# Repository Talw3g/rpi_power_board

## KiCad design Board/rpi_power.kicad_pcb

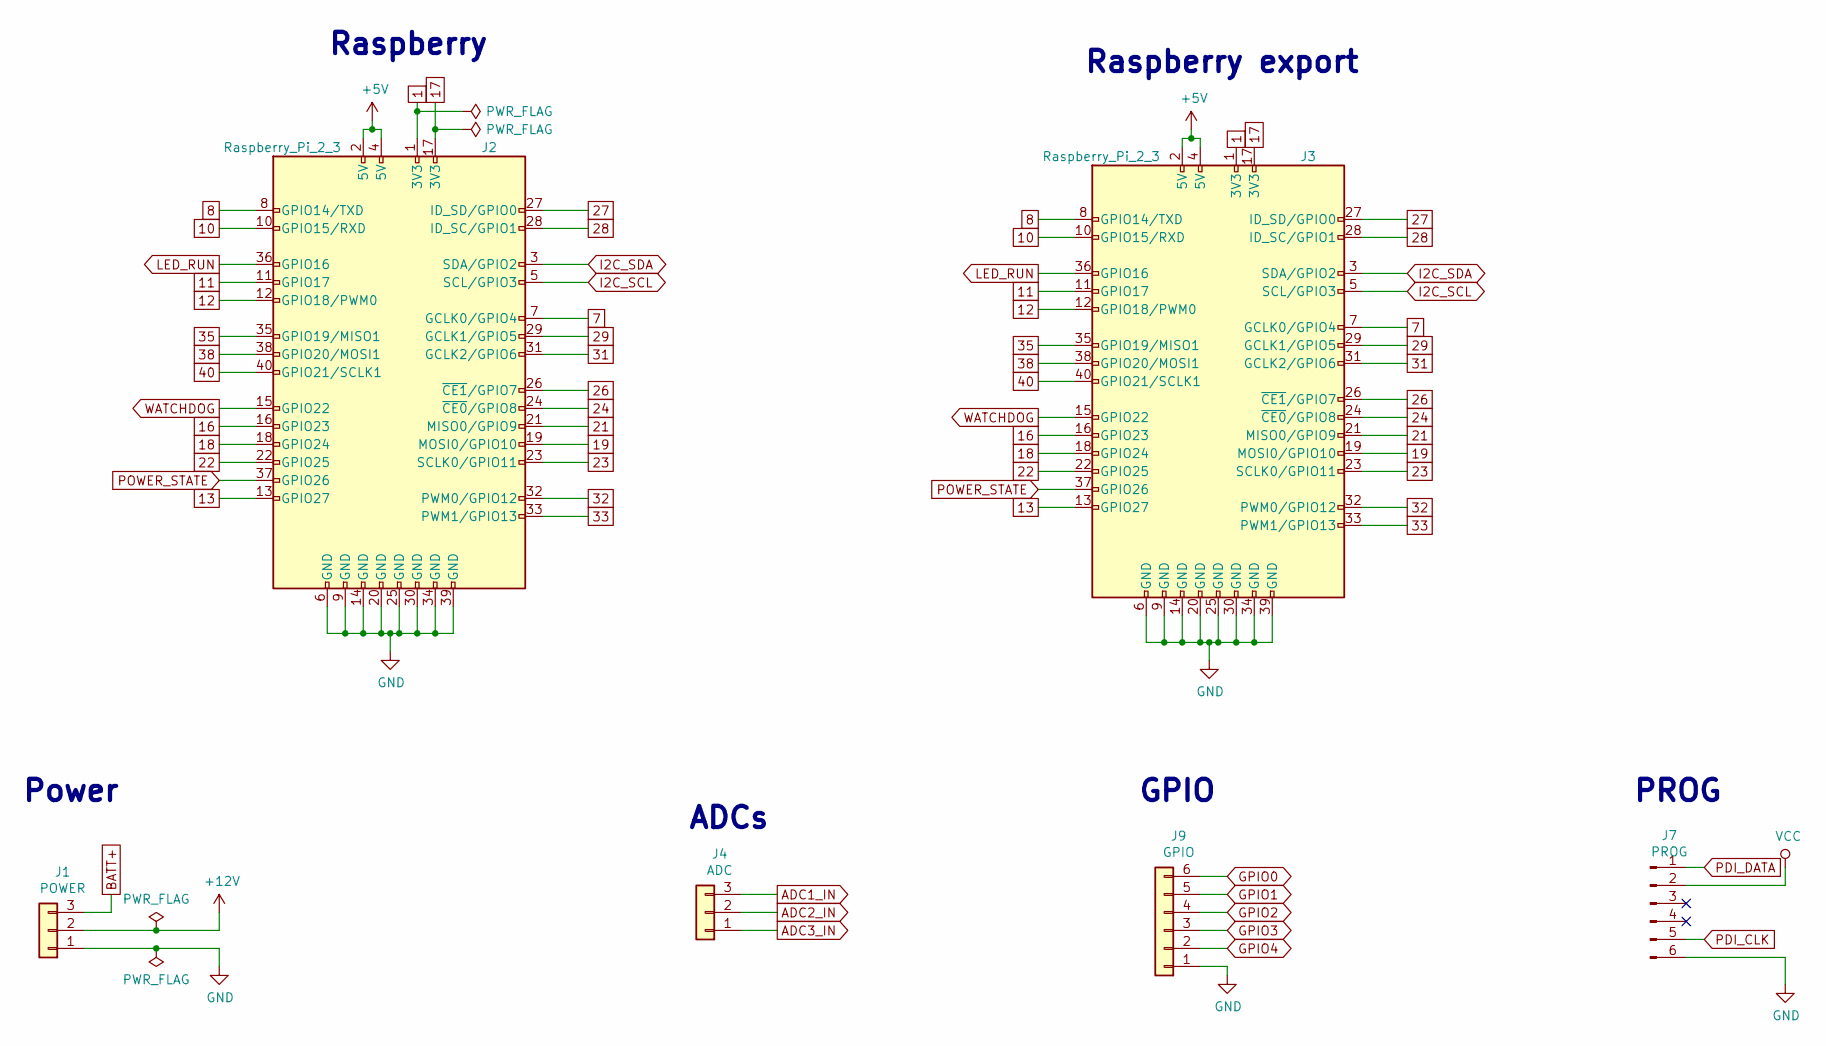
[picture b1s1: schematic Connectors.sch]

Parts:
J1: POWER; mpt_0,5-3-2,54; Farnell 3041360
J2: Raspberry_Pi_2_3; PinSocket_2x20_P2.54mm_Vertical_SMD; Farnell 2847933
J3: Raspberry_Pi_2_3; PinHeader_2x20_P2.54mm_Vertical_SMD; Farnell 2751390
J4: ADC; mpt_0,5-3-2,54; Farnell 3041360
J7: PROG; PinHeader_2x03_P2.54mm_Vertical
J9: GPIO; mpt_0,5-6-2,54; Farnell 3041426

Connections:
1: J2.1 (3V3), J3.1 (3V3)
7: J2.7 (GCLK0/GPIO4), J3.7 (GCLK0/GPIO4)
8: J2.8 (GPIO14/TXD), J3.8 (GPIO14/TXD)
10: J2.10 (GPIO15/RXD), J3.10 (GPIO15/RXD)
11: J2.11 (GPIO17), J3.11 (GPIO17)
12: J2.12 (GPIO18/PWM0), J3.12 (GPIO18/PWM0)
13: J2.13 (GPIO27), J3.13 (GPIO27)
16: J2.16 (GPIO23), J3.16 (GPIO23)
17: J2.17 (3V3), J3.17 (3V3)
18: J2.18 (GPIO24), J3.18 (GPIO24)
19: J2.19 (MOSI0/GPIO10), J3.19 (MOSI0/GPIO10)
21: J2.21 (MISO0/GPIO9), J3.21 (MISO0/GPIO9)
22: J2.22 (GPIO25), J3.22 (GPIO25)
23: J2.23 (SCLK0/GPIO11), J3.23 (SCLK0/GPIO11)
24: J2.24 (~CE0~/GPIO8), J3.24 (~CE0~/GPIO8)
26: J2.26 (~CE1~/GPIO7), J3.26 (~CE1~/GPIO7)
27: J2.27 (ID_SD/GPIO0), J3.27 (ID_SD/GPIO0)
28: J2.28 (ID_SC/GPIO1), J3.28 (ID_SC/GPIO1)
29: J2.29 (GCLK1/GPIO5), J3.29 (GCLK1/GPIO5)
31: J2.31 (GCLK2/GPIO6), J3.31 (GCLK2/GPIO6)
32: J2.32 (PWM0/GPIO12), J3.32 (PWM0/GPIO12)
33: J2.33 (PWM1/GPIO13), J3.33 (PWM1/GPIO13)
35: J2.35 (GPIO19/MISO1), J3.35 (GPIO19/MISO1)
38: J2.38 (GPIO20/MOSI1), J3.38 (GPIO20/MOSI1)
40: J2.40 (GPIO21/SCLK1), J3.40 (GPIO21/SCLK1)
+5V: J2.2 (5V), J2.4 (5V), J3.2 (5V), J3.4 (5V); also elsewhere on the board
+12V: J1.2; also elsewhere on the board
ADC1_IN: J4.3; also elsewhere on the board
ADC2_IN: J4.2; also elsewhere on the board
ADC3_IN: J4.1; also elsewhere on the board
BATT+: J1.3; also elsewhere on the board
GND: J1.1, J2.6 (GND), J2.9 (GND), J2.14 (GND), J2.20 (GND), J2.25 (GND), J2.30 (GND), J2.34 (GND), J2.39 (GND), J3.6 (GND), J3.9 (GND), J3.14 (GND), J3.20 (GND), J3.25 (GND), J3.30 (GND), J3.34 (GND), J3.39 (GND), J7.6, J9.1; also elsewhere on the board
GPIO0: J9.6; also elsewhere on the board
GPIO1: J9.5; also elsewhere on the board
GPIO2: J9.4; also elsewhere on the board
GPIO3: J9.3; also elsewhere on the board
GPIO4: J9.2; also elsewhere on the board
I2C_SCL: J2.5 (SCL/GPIO3), J3.5 (SCL/GPIO3); also elsewhere on the board
I2C_SDA: J2.3 (SDA/GPIO2), J3.3 (SDA/GPIO2); also elsewhere on the board
LED_RUN: J2.36 (GPIO16), J3.36 (GPIO16); also elsewhere on the board
PDI_CLK: J7.5; also elsewhere on the board
PDI_DATA: J7.1; also elsewhere on the board
POWER_STATE: J2.37 (GPIO26), J3.37 (GPIO26); also elsewhere on the board
VCC: J7.2; also elsewhere on the board
WATCHDOG: J2.15 (GPIO22), J3.15 (GPIO22); also elsewhere on the board

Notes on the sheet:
Raspberry
Power
ADCs
PROG
GPIO
Raspberry export

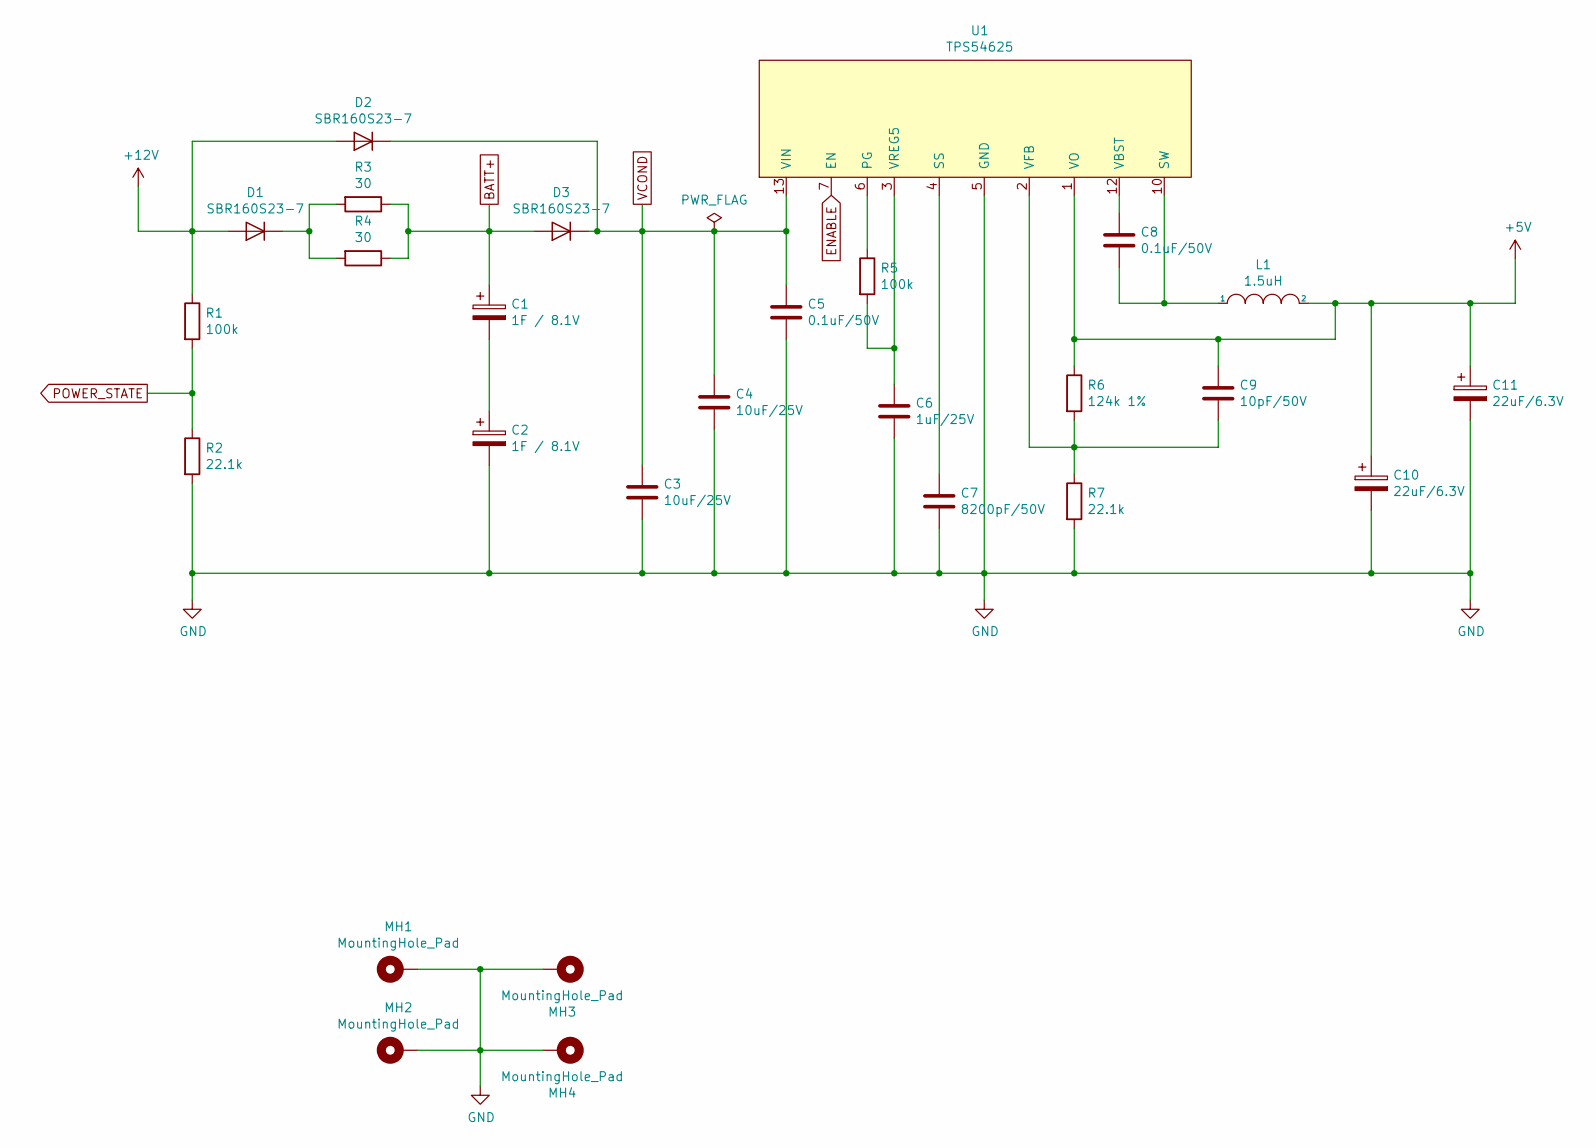
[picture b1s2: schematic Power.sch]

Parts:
C1, C2: 1F / 8.1V; SCMR22J105SRBA0_vertical; Farnell 2856949
C3, C4: 10uF/25V; C_0805_2012Metric_Pad1.15x1.40mm_HandSolder
C5, C8: 0.1uF/50V; C_0603_1608Metric_Pad1.05x0.95mm_HandSolder
C6: 1uF/25V; C_0805_2012Metric_Pad1.15x1.40mm_HandSolder
C7: 8200pF/50V; C_0603_1608Metric_Pad1.05x0.95mm_HandSolder
C9: 10pF/50V; C_0603_1608Metric_Pad1.05x0.95mm_HandSolder
C10, C11: 22uF/6.3V; Tantalum_SMD_3216_KEMET_T491_HandSolder; Farnell 2321204
D1, D2, D3: SBR160S23-7; D_SOT-23_ANK; Farnell 1863724
L1: 1.5uH; L_7.1x6.5_H3; Farnell 2215610
MH1, MH2, MH3, MH4: MountingHole_Pad; MountingHole_M3-5.8_Pad_Via
R1, R5: 100k; R_0603_1608Metric_Pad1.05x0.95mm_HandSolder
R2, R7: 22.1k; R_0603_1608Metric_Pad1.05x0.95mm_HandSolder
R3, R4: 30; TE_SM5; Farnell 2331667
R6: 124k 1%; R_0603_1608Metric_Pad1.05x0.95mm_HandSolder
U1: TPS54625; HTSSOP-14-PWP_Handsolder; Farnell 2361244

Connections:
+5V: C9.1, C10.1, C11.1, L1.2, R6.1, U1.1 (VO); also elsewhere on the board
+12V: D1.2 (A), D2.2 (A), R1.1; also elsewhere on the board
BATT+: C1.1, D3.2 (A), R3.1, R4.1; also elsewhere on the board
ENABLE: U1.7 (EN); also elsewhere on the board
GND: C2.2, C3.2, C4.2, C5.2, C6.2, C7.2, C10.2, C11.2, MH1.1, MH2.1, MH3.1, MH4.1, R2.2, R7.2, U1.5 (GND), U1.8 (GND), U1.9 (GND), U1.15 (GND); also elsewhere on the board
unnamed: C1.2, C2.1
unnamed: C6.1, R5.2, U1.3 (VREG5)
unnamed: C7.1, U1.4 (SS)
unnamed: C8.1, U1.12 (VBST)
unnamed: C8.2, L1.1, U1.10 (SW), U1.11 (SW)
unnamed: C9.2, R6.2, R7.1, U1.2 (VFB)
unnamed: D1.1 (K), R3.2, R4.2
unnamed: R5.1, U1.6 (PG)
POWER_STATE: R1.2, R2.1; also elsewhere on the board
VCOND: C3.1, C4.1, C5.1, D2.1 (K), D3.1 (K), U1.13 (VIN), U1.14 (VIN); also elsewhere on the board

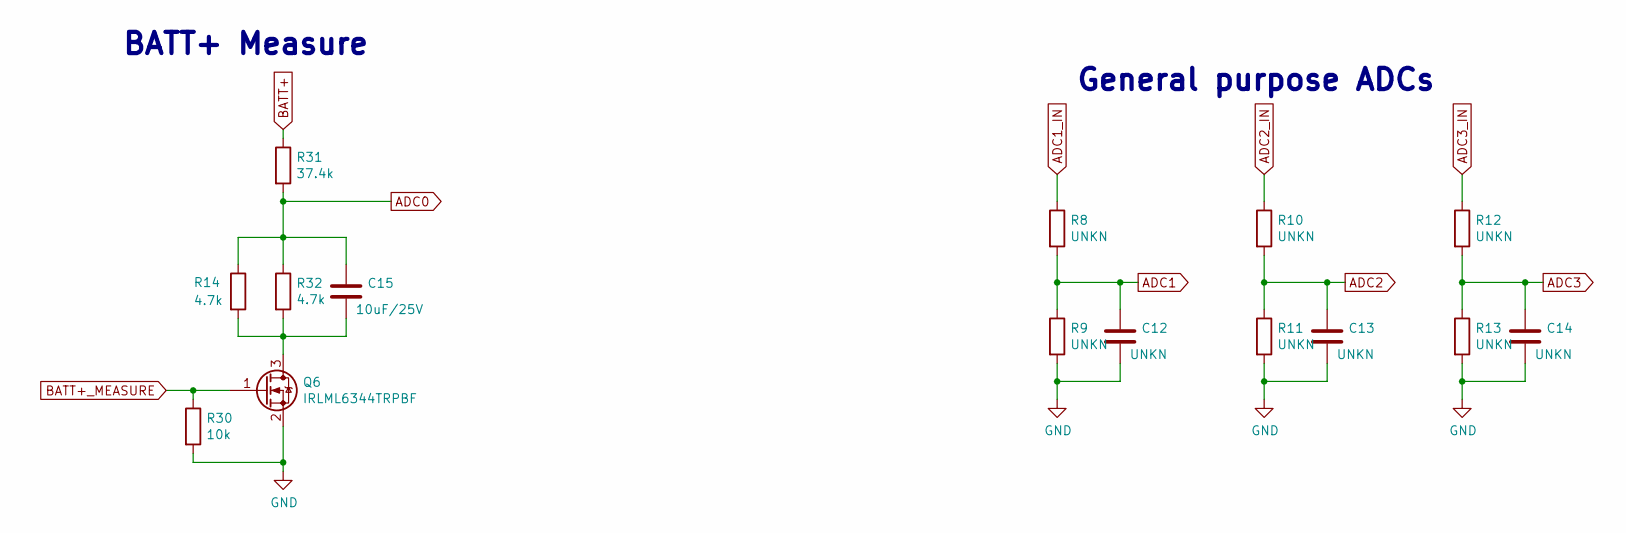
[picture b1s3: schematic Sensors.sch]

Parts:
C12, C13, C14: UNKN; C_0603_1608Metric_Pad1.05x0.95mm_HandSolder
C15: 10uF/25V; C_0603_1608Metric_Pad1.05x0.95mm_HandSolder
Q6: IRLML6344TRPBF; SOT-23_Handsoldering; Farnell IRLML6344TRPBF
R8, R9, R10, R11, R12, R13: UNKN; R_0603_1608Metric_Pad1.05x0.95mm_HandSolder
R14, R32: 4.7k; R_0603_1608Metric_Pad1.05x0.95mm_HandSolder
R30: 10k; R_0603_1608Metric_Pad1.05x0.95mm_HandSolder
R31: 37.4k; R_0603_1608Metric_Pad1.05x0.95mm_HandSolder

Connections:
ADC0: C15.1, R14.1, R31.2, R32.1; also elsewhere on the board
ADC1: C12.1, R8.2, R9.1; also elsewhere on the board
ADC1_IN: R8.1; also elsewhere on the board
ADC2: C13.1, R10.2, R11.1; also elsewhere on the board
ADC2_IN: R10.1; also elsewhere on the board
ADC3: C14.1, R12.2, R13.1; also elsewhere on the board
ADC3_IN: R12.1; also elsewhere on the board
BATT+: R31.1; also elsewhere on the board
BATT+_MEASURE: Q6.1 (G), R30.1; also elsewhere on the board
GND: C12.2, C13.2, C14.2, Q6.2 (S), R9.2, R11.2, R13.2, R30.2; also elsewhere on the board
unnamed: C15.2, Q6.3 (D), R14.2, R32.2

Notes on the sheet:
BATT+ Measure
General purpose ADCs

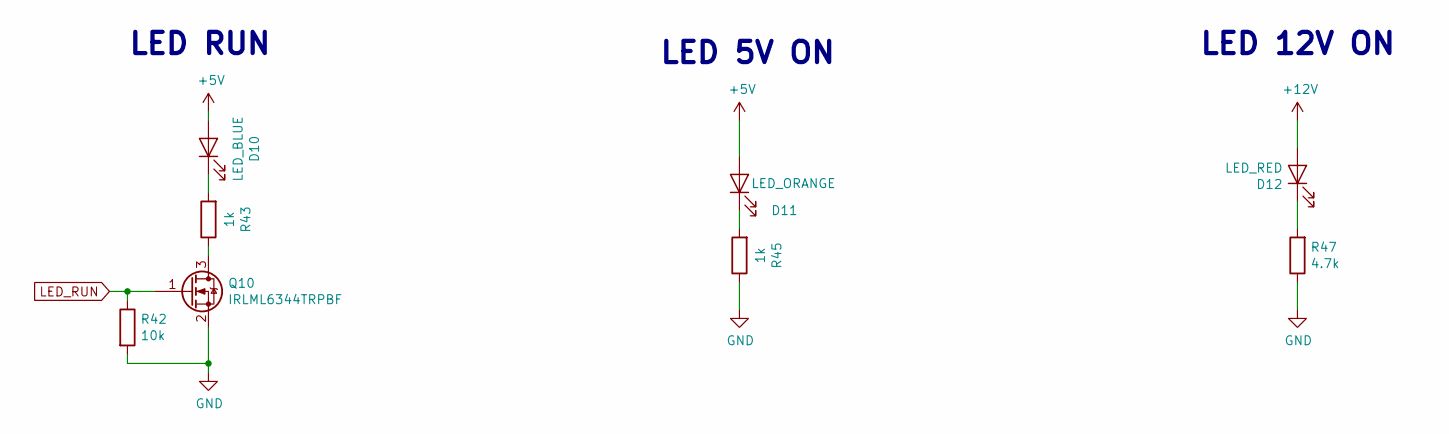
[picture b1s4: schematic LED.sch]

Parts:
D10: LED_BLUE; LED_0603_1608Metric_Pad1.05x0.95mm_HandSolder; Farnell 2251459
D11: LED_ORANGE; LED_0603_1608Metric_Pad1.05x0.95mm_HandSolder; Farnell 2251473
D12: LED_RED; LED_0603_1608Metric_Pad1.05x0.95mm_HandSolder; Farnell 2251484
Q10: IRLML6344TRPBF; SOT-23_Handsoldering; Farnell IRLML6344TRPBF
R42: 10k; R_0603_1608Metric_Pad1.05x0.95mm_HandSolder
R43, R45: 1k; R_0603_1608Metric_Pad1.05x0.95mm_HandSolder
R47: 4.7k; R_0603_1608Metric_Pad1.05x0.95mm_HandSolder

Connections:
+5V: D10.2 (A), D11.2 (A); also elsewhere on the board
+12V: D12.2 (A); also elsewhere on the board
GND: Q10.2 (S), R42.2, R45.1, R47.1; also elsewhere on the board
LED_RUN: Q10.1 (G), R42.1; also elsewhere on the board
unnamed: D10.1 (K), R43.2
unnamed: D11.1 (K), R45.2
unnamed: D12.1 (K), R47.2
unnamed: Q10.3 (D), R43.1

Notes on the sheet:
LED RUN
LED 5V ON
LED 12V ON

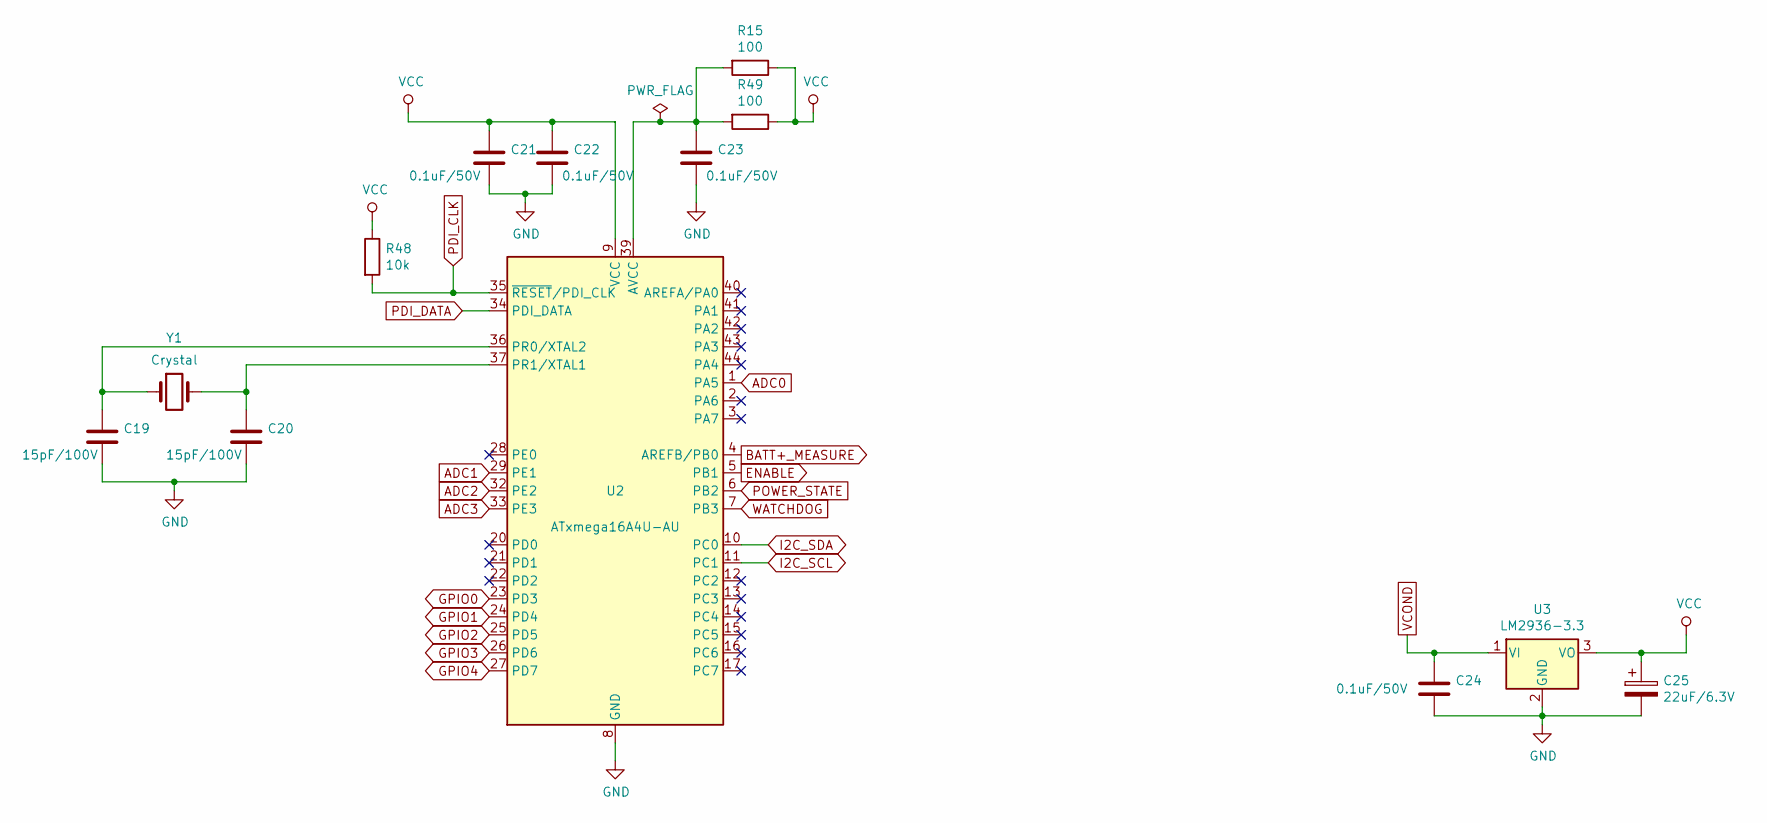
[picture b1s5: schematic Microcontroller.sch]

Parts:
C19, C20: 15pF/100V; C_0603_1608Metric_Pad1.05x0.95mm_HandSolder
C21, C22, C23, C24: 0.1uF/50V; C_0603_1608Metric_Pad1.05x0.95mm_HandSolder
C25: 22uF/6.3V; Tantalum_SMD_3216_KEMET_T491_HandSolder; Farnell 2321204
R15, R49: 100; R_0603_1608Metric_Pad1.05x0.95mm_HandSolder
R48: 10k; R_0603_1608Metric_Pad1.05x0.95mm_HandSolder
U2: ATxmega16A4U-AU; TQFP-44_10x10mm_P0.8mm; Farnell 2066301
U3: LM2936-3.3; SOT-223; Farnell 1469062
Y1: Crystal; Crystal_SMD_Abracon_ABM3-2Pin_5.0x3.2mm; Farnell 2467791

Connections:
ADC0: U2.28 (PE0); also elsewhere on the board
ADC1: U2.29 (PE1); also elsewhere on the board
ADC2: U2.32 (PE2); also elsewhere on the board
ADC3: U2.33 (PE3); also elsewhere on the board
BATT+_MEASURE: U2.4 (AREFB/PB0); also elsewhere on the board
ENABLE: U2.5 (PB1); also elsewhere on the board
GND: C19.2, C20.2, C21.2, C22.2, C23.2, C24.2, C25.2, U2.8 (GND), U2.18 (GND), U2.30 (GND), U2.38 (GND), U3.2 (GND), U3.4; also elsewhere on the board
GPIO0: U2.23 (PD3); also elsewhere on the board
GPIO1: U2.24 (PD4); also elsewhere on the board
GPIO2: U2.25 (PD5); also elsewhere on the board
GPIO3: U2.26 (PD6); also elsewhere on the board
GPIO4: U2.27 (PD7); also elsewhere on the board
I2C_SCL: U2.11 (PC1); also elsewhere on the board
I2C_SDA: U2.10 (PC0); also elsewhere on the board
unnamed: C19.1, U2.36 (PR0/XTAL2), Y1.1
unnamed: C20.1, U2.37 (PR1/XTAL1), Y1.2
unnamed: C23.1, R15.2, R49.2, U2.39 (AVCC)
PDI_CLK: R48.2, U2.35 (~RESET~/PDI_CLK); also elsewhere on the board
PDI_DATA: U2.34 (PDI_DATA); also elsewhere on the board
POWER_STATE: U2.6 (PB2); also elsewhere on the board
VCC: C21.1, C22.1, C25.1, R15.1, R48.1, R49.1, U2.9 (VCC), U2.19 (VCC), U2.31 (VCC), U3.3 (VO); also elsewhere on the board
VCOND: C24.1, U3.1 (VI); also elsewhere on the board
WATCHDOG: U2.7 (PB3); also elsewhere on the board

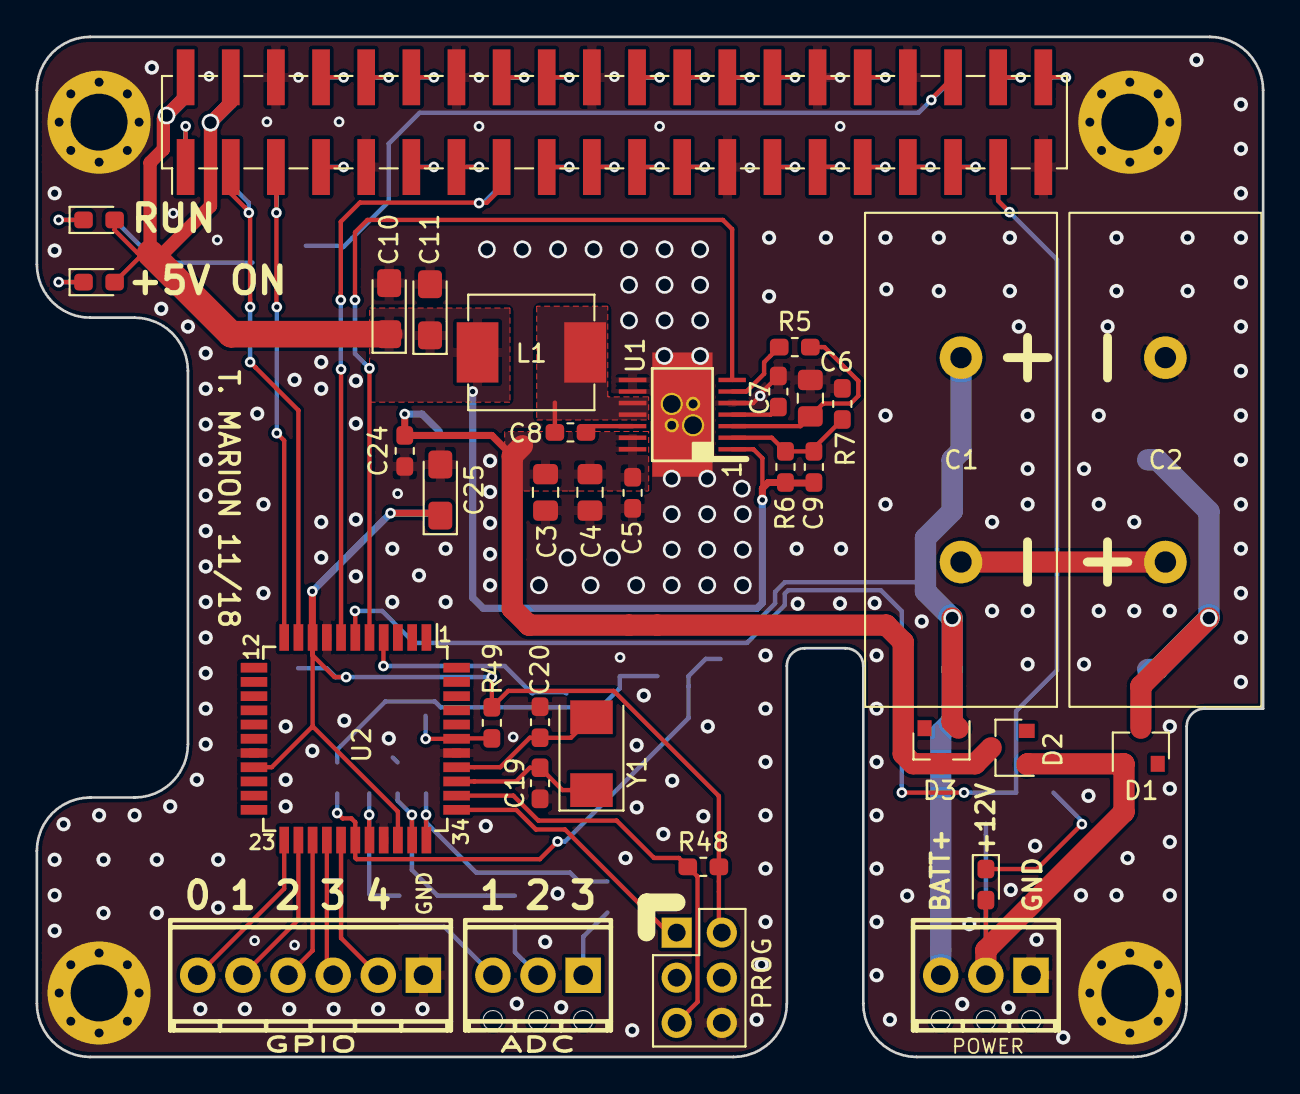
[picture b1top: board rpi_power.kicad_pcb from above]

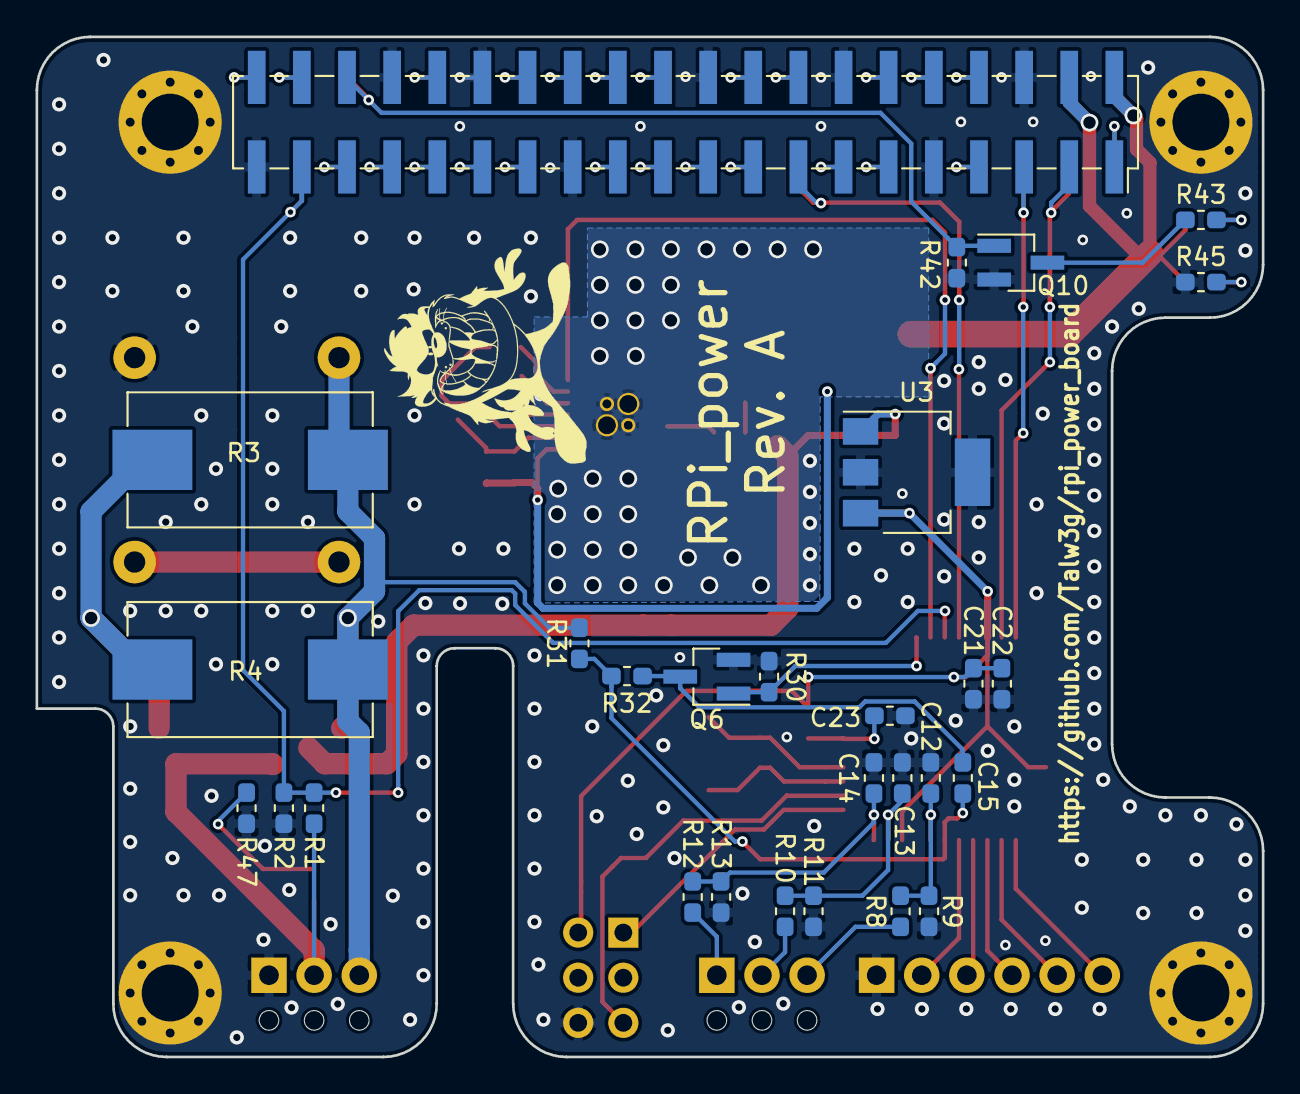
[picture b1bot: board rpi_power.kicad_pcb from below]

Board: 2 copper layers, 69.0 x 57.4 mm, 67 parts (28 on the bottom side), 68 nets.

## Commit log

2018-10-26 Schematic done, pending review.
2018-10-27 Changed supercap ref, updated some footprints.
2018-10-28 Replaced wirepads by phoenix connectors.
2018-10-30 Routing in progress.
2018-10-30 Branched from cellar_board repo. Cleaned up unnecessary items.
2018-10-30 Components placed.
2018-10-31 Small changes to components positions.
2018-10-31 Updated some footprints.
2018-11-01 Routing done, pending review.
2018-11-01 Routing and silkscreen done.
2018-11-02 Differentiated VCOND and BATT+. Routing done.
2018-11-02 Small tweaks.
2018-11-02 Gerber files generated.
2018-11-02 Forgot to save before commit...
2018-11-03 Corrected silkscreen.
2018-11-13 Removed useless "rpi_power" folder.
2018-11-13 Updated gitignore.
2018-11-13 Updated some refs.
2018-11-16 Minor modifications.
2018-12-09 Moved board files to specific folder.
2018-12-10 Added protection resistors on xmega GPIOs. Corrected prog connector outline.
2018-12-11 Draft for power management code.
2018-12-11 Basic logic working.
2018-12-11 Tried to implement watchdog toggling.
2018-12-12 WIP on sleep implementation.
2018-12-12 Sleep now working, but watchdog not anymore.
2018-12-13 Sleep AND wathdog working.
2018-12-14 Some corrections.
2018-12-14 MAJOR CORRECTION: moved ADCs to correct port on xmega. Added a LED controlled by the xmega.
2018-12-18 WIP on ADC support.
2020-04-20 WIP on battery voltage measure
2020-04-27 Some mod to track actual board status.
2020-05-01 Added software part
